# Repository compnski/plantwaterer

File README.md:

# plantwaterer

# Plant Waterer v2.
 A robotic plant watering system in two parts.

embeddedwaterer: Tinygo program for a microcontroller that waters on a fixed schedule.
watererserver: Go program for rasberryPI that communicates with the embedded application to report stat and control remotely.
Currently is a standalone parser that emits CSVs with stats data.

## Big Features:
* Soil humidity sensors
* Multiple relays, allows different water circuits
* Read stats / update config remotely
* Webcam for monitoring, takes snapshots

## Arduino
* Turns relays on/off for specified on/off periods.
* Takes commands, sends stats back over serial.
* Monitors humidity sensors, reports back to Pi

### Future Plans
* Humidity based control, water when soil dries past certain threshold
* Store customization data in EEPROM

## Raspberry Pi
* Currently just records serial data to disk for later analysis
* Takes webcam snapshot every 5 minutes

### Future Plans
* Simple go service, hosts website.
* Polls Arduino via serial link on some interval. Keeps state of last values to show deltas.
* If Arduino resets, Pi monitor should automatically reset the water on/off durations if they’ve been changed.
* Awair integration to pull in room humidity/temp/co2 levels

## Serial Link
More details on the linux side in the pi/README.md, and the hardware side in hardware/README.md
In general, standard arduino serial at 115200 baud.

3-byte header, 4-byte request
Request: `CMD <command> <8bit number> <16bit number>`
Response: Echo command back. Stats is special and will then send stats followed by a terminator.

### Commands
| command                	| value 	| args?                                	| Notes                                                	|   	|
|------------------------	|-------	|--------------------------------------	|------------------------------------------------------	|---	|
| water_on               	| 0x02  	| 8bit water id                        	| Resets water timer                                   	|   	|
| water_off              	| 0x03  	| 8bit water id                        	| Resets water time                                    	|   	|
| set_water_on_duration  	| 0x04  	| 8bit water id 16bit duration seconds 	|                                                      	|   	|
| set_water_off_duration 	| 0x05  	| 8bit water id 16bit duration seconds 	|                                                      	|   	|
| set_next_water_at      	| 0x06  	| 8bit sensor id 16bit value           	| Sets wait time to desired value. Useful after resets 	|   	|

To send a command, echo over the serial link.
`echo -e 'CMD\x03\x00\x00\x00' > /dev/serial0`

### Stats Return:
Stats are continually sent via serial every StatsIntervalSeconds, default of 5.

``` json
{"now": 1485775,
"sensors":[
 {"id": 0, "d":[ 1, 37440, 2, 37376, 3, 37376, 4, 37440, 5, 37440 ]},
 {"id": 1, "d":[ 1, 37376, 2, 37440, 3, 37376, 4, 37376, 5, 37376 ]}
],"sections":[
 {"id": 0, "on": false, "next": 1555513, "last": 1296313, 
 "onTime": 50, "offTime": 259200, 
 "onAcc": 306, "offAcc": 1296007 }
]}
```

Notes:
* Number of sensors and length of history is determined at compile-time. It is limited by the memory capacity of your chip. More powerful chips can support more sensors and longer histories.
* All timestamps are relative to the local epoch, when the board was turned on.
* The data in sensors.d are pairs of (timestamp, value) from the analog input. 
* onTime / offTime are current status values
* onAcc / offAcc accumulate time spent in on / off states over time

## References
* https://github.com/huin/goserial
* https://www.digikey.com/product-detail/en/adafruit-industries-llc/997/1528-2003-ND/6827136
* https://tinygo.org/
* https://github.com/d2r2/go-i2c
* http://www.krekr.nl/wp-content/uploads/2013/08/Arduino-uno.pdf
* https://www.raspberrypi.org/documentation/hardware/raspberrypi/mechanical/rpi_MECH_3b_1p2.pdf
* https://www.youtube.com/watch?v=ioSYlxHlYdI (For solenoid board design)
* https://jlcpcb.com/ - Cheap PCB!
* https://www.ti.com/lit/ds/symlink/sn74hc595.pdf
* https://www.ti.com/lit/ds/symlink/uln2803a.pdf?

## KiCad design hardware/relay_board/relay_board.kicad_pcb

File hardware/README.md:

# Watering

## Emitters

[Side-In Waterer](https://www.tinkercad.com/things/kaySP06Uaiy-side-in-waterer)

## Tubing
This project is using 5/16" ID hardware.
I'm currently using Vinyl tubing but it's very inflexible and hard to set up. Next time I set the system up, I plan to try the Silicone based tubing.

## Pump and Water Source
I use a submersible 12v pump, linked below. It delivers 280L/H, which is ~3.9L in the 50 seconds I run it.

I put this in the tank of an auto-filling resivior (toliet) so it has an "infinite" source of water without manual filling.
Preventing the siphon effect is very important with this setup. I have a few holes in the tube just inside the tank to allow in air. This prevents a vacuum from forming and pulling water past the pump after it is stopped.

## Parts I used
* Pump: https://www.amazon.com/gp/product/B00JWJIC0K
* Vinyl Tubing: https://www.amazon.com/gp/product/B000E62TCC
* T-Connector: https://www.amazon.com/gp/product/B0040CRX0Y/
* Silicone Tubing: https://www.amazon.com/Silicon-JoyTube-Silicone-Brewing-Winemaking/dp/B07T8SBX3Y/

## Important Notes
* Anti-Siphon hole

# Pi <-> Arduino link

## Purpose

## Optocoupling
The Rasberry Pi uses 3.3v for TTL serial and the Arduino uses 5v. Additionally, they have separate power sources and may not share a ground. Thus, the serial link between them must be isolated. I used the <PART> for this, along with a transitor because the output is inverted.
There are two of these, one for each direction.
The RST line of the Arduino is also isolated and connected to a GPIO pin on the Pi in case a reset is needed. This uses a slower, but simpler <PART>.
[KiCad schematic]()
[Breadboard]()

## Moisture Sensing
### Multiplexing
### Direct Connection

## Relay Board (Work In Progress)
Eventu
Relay Board:
* Shift Register - https://www.ti.com/lit/ds/symlink/sn74hc595.pdf
* Transistors    - https://www.ti.com/lit/ds/symlink/uln2803a.pdf
* LED Display    - https://optoelectronics.liteon.com/upload/download/DS-30-92-0810/LTA-1000HR.pdf
* Resistor Netwrk- https://www.bourns.com/docs/Product-Datasheets/4600x.pdf
* Relay          - https://content.kemet.com/datasheets/KEM_R7002_EC2_EE2.pdf

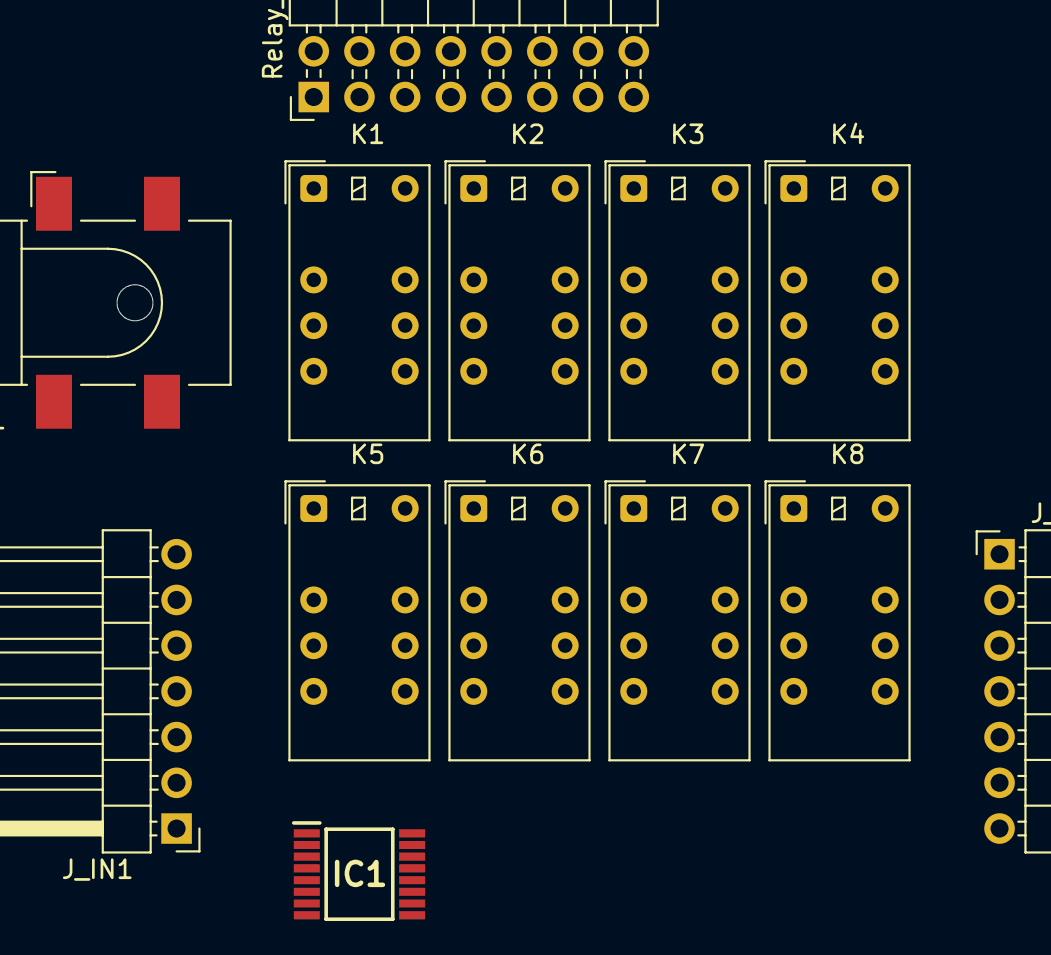
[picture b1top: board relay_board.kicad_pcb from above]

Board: 2 copper layers, 13 parts (0 on the bottom side), 33 nets, no tracks yet.

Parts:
IC1: MC74HCT595ADTG; SOP65P640X120-16N
J1: Barrel_Jack; BarrelJack_CLIFF_FC681465S_SMT_Horizontal
J_IN1: Conn_01x07_Male; PinHeader_1x07_P2.54mm_Horizontal
J_OUT1: Conn_01x07_Male; PinHeader_1x07_P2.54mm_Horizontal
K1, K2, K3, K4, K5, K6, K7, K8: EC2-5NU; Relay_DPDT_Kemet_EC2
Relay_Conn1: Conn_02x08_Odd_Even; PinHeader_2x08_P2.54mm_Horizontal

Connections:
+12V: J1.1, K1.4, K2.4, K3.4, K4.4, K5.4, K6.4, K7.4, K8.4
/k4_12v: K4.5, Relay_Conn1.7
/k4_gnd: K4.8, Relay_Conn1.8
/k5_12v: K5.5, Relay_Conn1.9
/k5_gnd: K5.8, Relay_Conn1.10
/k6_12v: K6.5, Relay_Conn1.11
/k6_gnd: K6.8, Relay_Conn1.12
/k7_12v: K7.5, Relay_Conn1.13
/k7_gnd: K7.8, Relay_Conn1.14
/k8_12v: K8.5, Relay_Conn1.15
/k8_gnd: K8.8, Relay_Conn1.16
GND: IC1.8, J1.2, J_IN1.1, J_OUT1.1, K1.9, K1.12, K2.9, K2.12, K3.9, K3.12, K4.9, K4.12, K5.9, K5.12, K6.9, K6.12, K7.9, K7.12, K8.9, K8.12
unnamed: IC1.1, K2.1
unnamed: IC1.2, K3.1
unnamed: IC1.3, K4.1
unnamed: IC1.4, K5.1
unnamed: IC1.5, K6.1
unnamed: IC1.6, K7.1
unnamed: IC1.7, K8.1
unnamed: IC1.9, J_OUT1.6
unnamed: IC1.10, J_IN1.2, J_OUT1.2
unnamed: IC1.11, J_IN1.3, J_OUT1.3
unnamed: IC1.12, J_IN1.4, J_OUT1.4
unnamed: IC1.13, J_IN1.5, J_OUT1.5
unnamed: IC1.14, J_IN1.6
unnamed: IC1.15, K1.1
unnamed: K1.5, Relay_Conn1.1
unnamed: K1.8, Relay_Conn1.2
unnamed: K2.5, Relay_Conn1.3
unnamed: K2.8, Relay_Conn1.4
unnamed: K3.5, Relay_Conn1.5
unnamed: K3.8, Relay_Conn1.6
VCC: IC1.16, J_IN1.7, J_OUT1.7

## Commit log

2020-08-06 Initialize README.md with plan
2020-09-18 Add hardware schematics
2020-09-18 Stub commands
2020-09-18 Legacy C plant waterer
2020-09-18 Initial WIP for tinygo plantwaterer
2020-09-20 Gather data from moisture sensors on interval
    Add interrupt driven clock. This breaks time.Sleep.
    Insead, track and drive the event loop manually.
2020-09-20 Remove extraneous include
2020-09-21 Clean up moisture monitoring to another file.
    Start groundwork for water system and scheduling
2020-09-26 Add water sections and schedules.
    Only one schedule per section. Set OnSeconds, OffSeconds.
    Eventually controllable via RasbPi
2020-09-27 ignore built files
2020-09-27 Start framework connection to RasbPi
    Add start of command class to control schedule and report stats
2020-10-08 It works!! Succesfully reads commands from PI, sends JSON data
2020-10-11 Clean up and start moving some code into packages
2020-10-11 Remove unneeded sr.py
2020-10-11 Fixup
2020-11-06 Add KiCad schematic for interconnect
2020-11-06 Add code to parse stats JSON and output as CSV for plotting
2020-11-06 Split README contents better into folders
2020-11-06 Scripts and configs for the Pi
